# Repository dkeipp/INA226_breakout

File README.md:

# INA226_breakout

Created with Eagle 7.7

It's just a draft at the moment.

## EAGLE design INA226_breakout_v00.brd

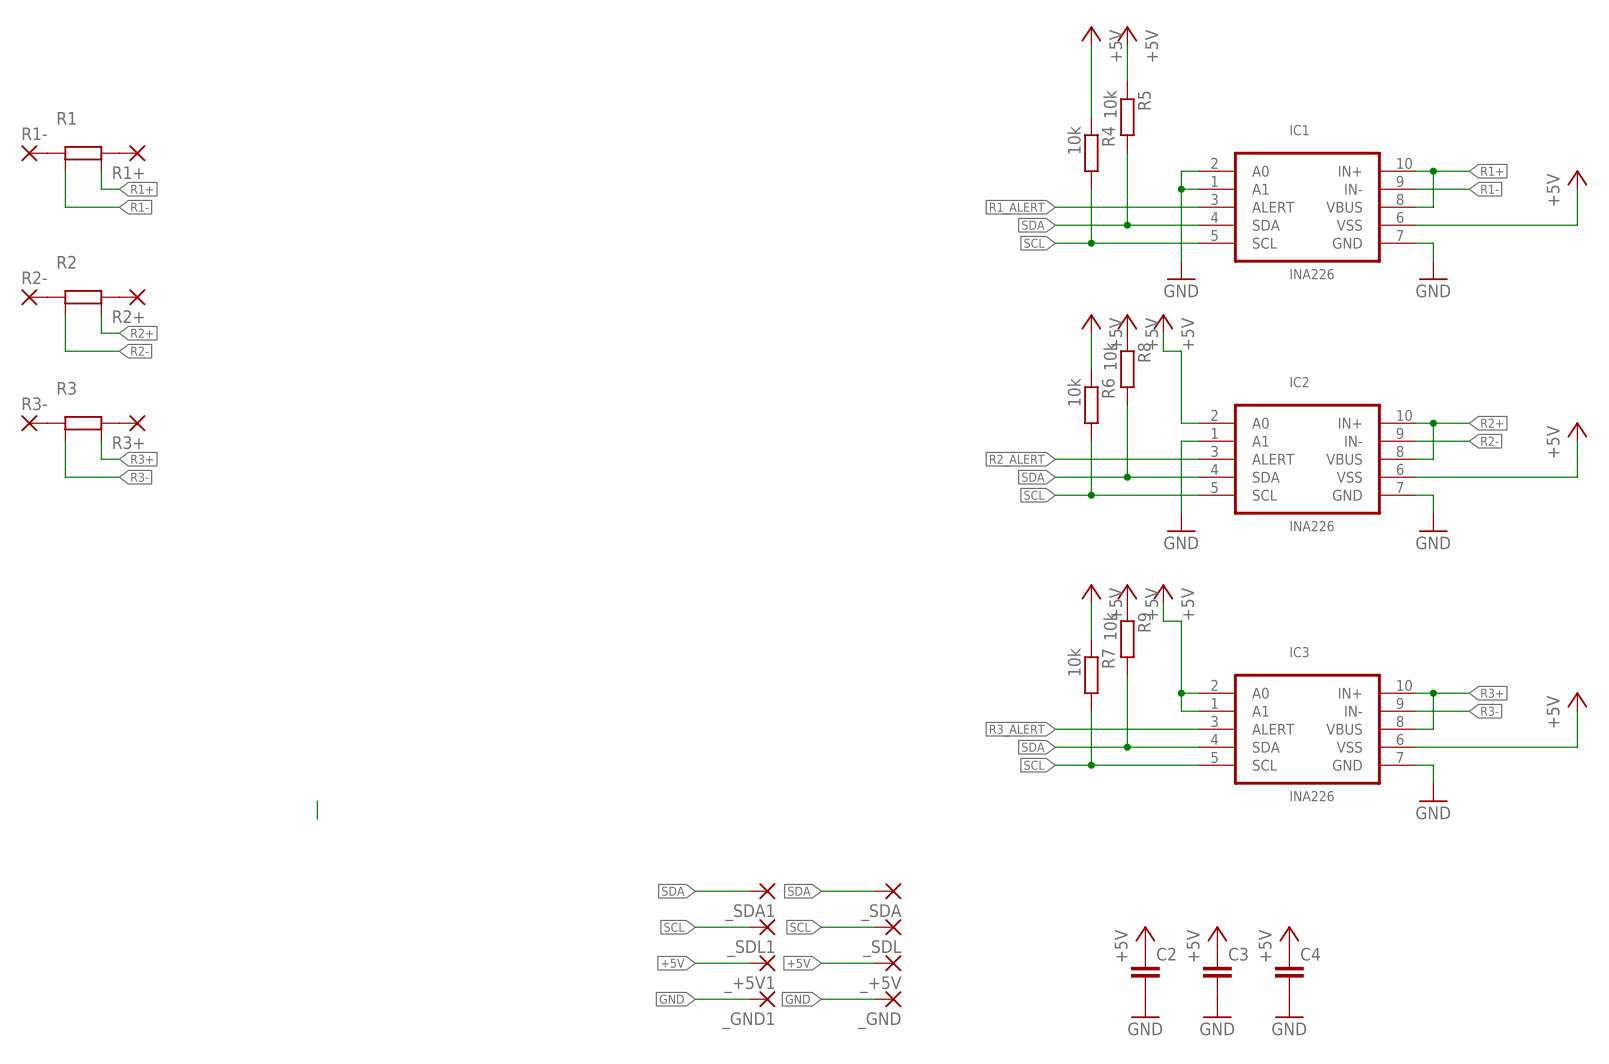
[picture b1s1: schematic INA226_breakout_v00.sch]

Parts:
C2, C3: C-EUC0805; C0805
C4: C-EUC0603; C0603
IC1, IC2, IC3: INA226; VSSOP-10
R1, R2, R3: BOURNS_CSS4J-4026
R1+, R1-, R2+, R2-, R3+, R3-: 3,81/1,4
R4, R5, R6, R7, R8, R9: 10k; M0805
_+5V, _+5V1: 1,6/0,9
_GND, _GND1: 1,6/0,9
_SDA, _SDA1: 1,6/0,9
_SDL, _SDL1: 1,6/0,9

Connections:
+5V: C2.1, C3.1, C4.1, IC1.6 (VSS), IC2.2 (A0), IC2.6 (VSS), IC3.1 (A1), IC3.2 (A0), IC3.6 (VSS), R4.1, R5.1, R6.1, R7.1, R8.1, R9.1, _+5V.1, _+5V1.1
GND: C2.2, C3.2, C4.2, IC1.1 (A1), IC1.2 (A0), IC1.7 (GND), IC2.1 (A1), IC2.7 (GND), IC3.7 (GND), _GND.1, _GND1.1
unnamed: R1.P$1 (1), R1-.1
unnamed: R2.P$1 (1), R2-.1
unnamed: R3.P$1 (1), R3-.1
unnamed: R1.P$2 (2), R1+.1
unnamed: R2.P$2 (2), R2+.1
unnamed: R3.P$2 (2), R3+.1
R1+: IC1.8 (VBUS), IC1.10 (IN+), R1.PS$2 (S2)
R1-: IC1.9 (IN-), R1.PS$1 (S1)
R1_ALERT: IC1.3 (ALERT)
R2+: IC2.8 (VBUS), IC2.10 (IN+), R2.PS$2 (S2)
R2-: IC2.9 (IN-), R2.PS$1 (S1)
R2_ALERT: IC2.3 (ALERT)
R3+: IC3.8 (VBUS), IC3.10 (IN+), R3.PS$2 (S2)
R3-: IC3.9 (IN-), R3.PS$1 (S1)
R3_ALERT: IC3.3 (ALERT)
SCL: IC1.5 (SCL), IC2.5 (SCL), IC3.5 (SCL), R4.2, R6.2, R7.2, _SDL.1, _SDL1.1
SDA: IC1.4 (SDA), IC2.4 (SDA), IC3.4 (SDA), R5.2, R8.2, R9.2, _SDA.1, _SDA1.1

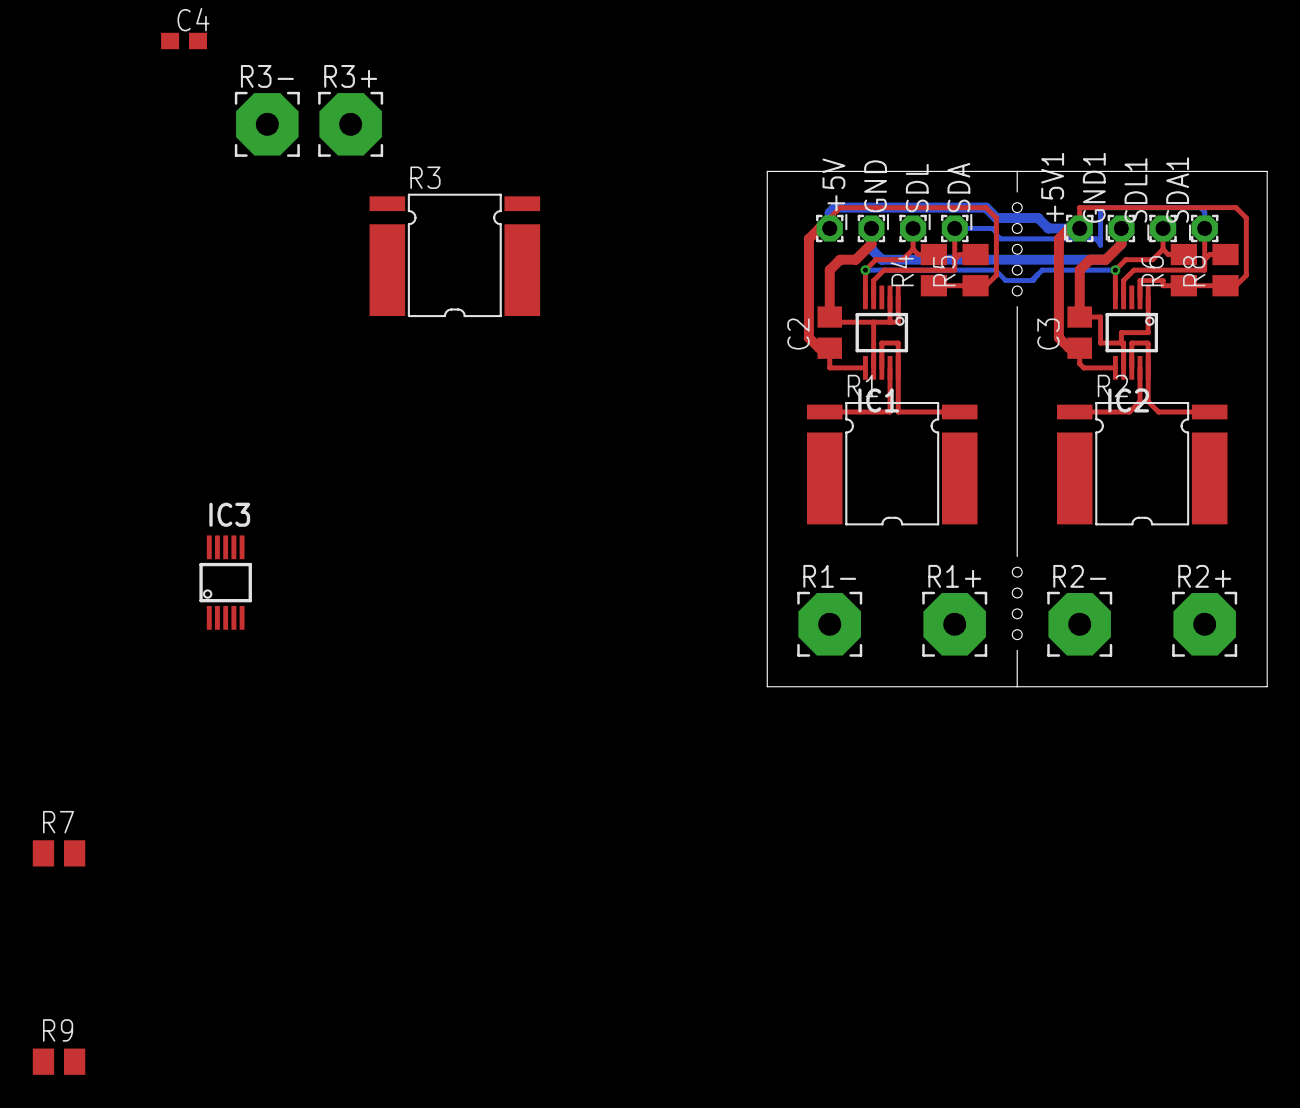
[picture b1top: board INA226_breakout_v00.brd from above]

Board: 2 copper layers, 30.5 x 31.4 mm, 29 parts (0 on the bottom side), 16 nets.

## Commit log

2017-09-28 first draft
2017-09-29 Short description
